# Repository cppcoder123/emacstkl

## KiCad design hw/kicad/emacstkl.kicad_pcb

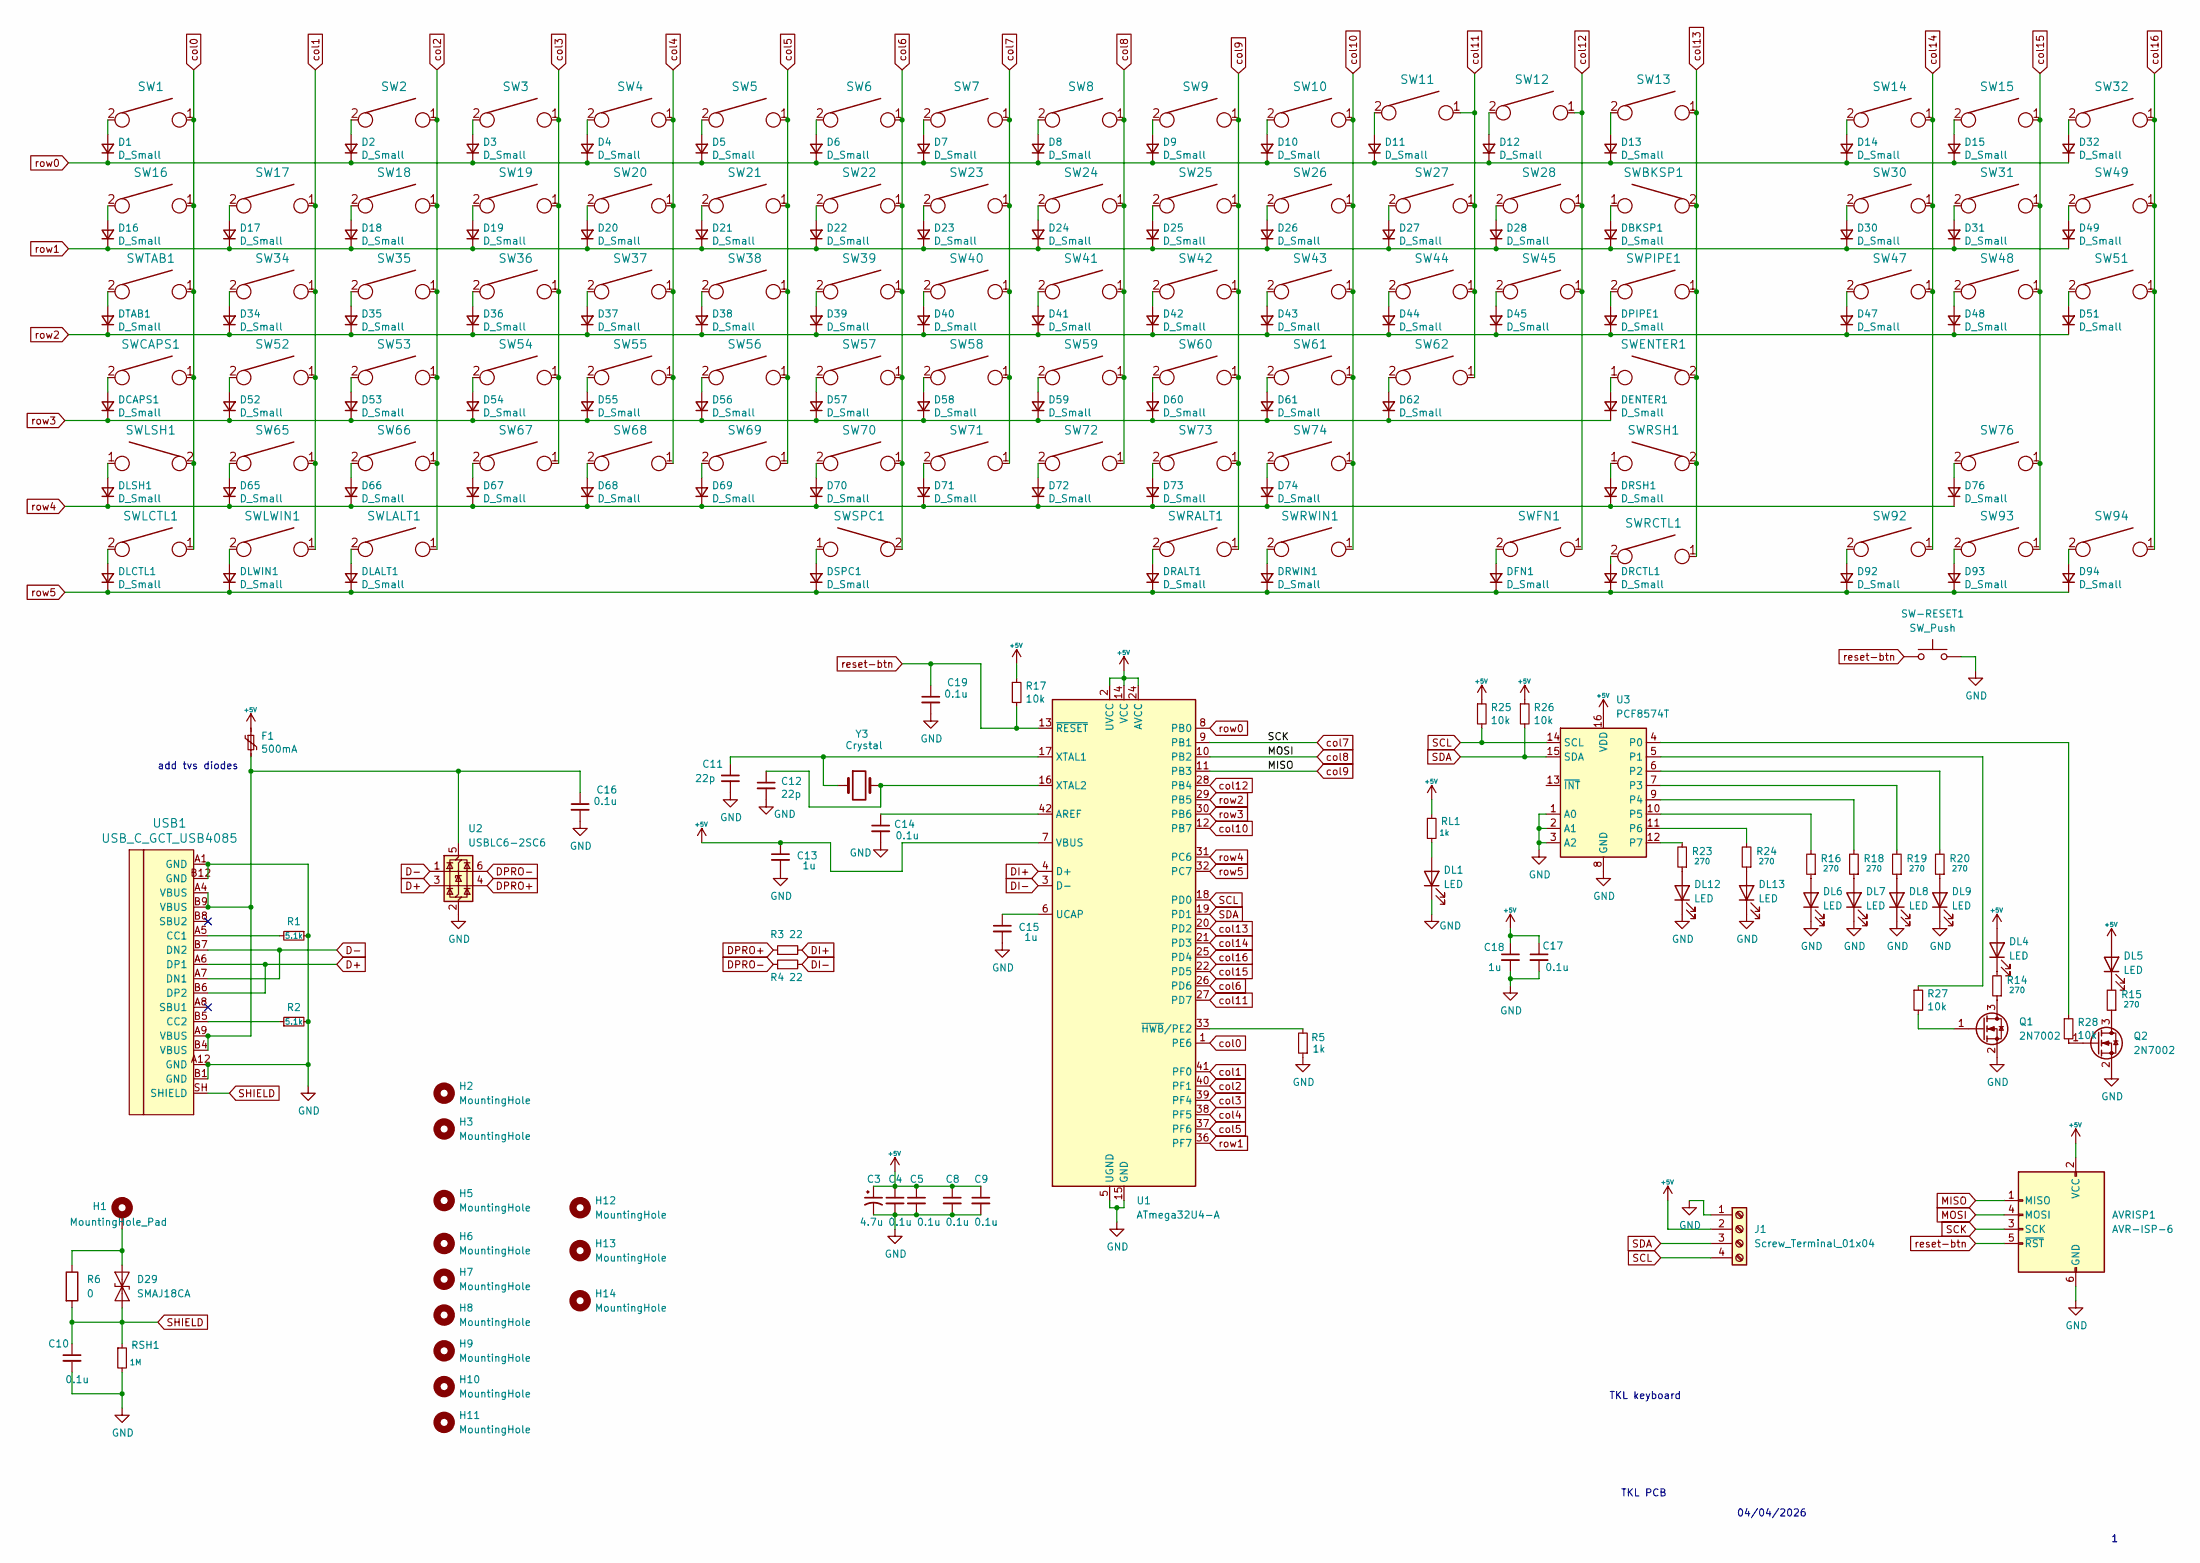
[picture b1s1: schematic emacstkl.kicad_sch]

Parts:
AVRISP1: AVR-ISP-6; PinHeader_2x03_P2.54mm_Vertical
C3: 4.7u; CP_Radial_D4.0mm_P1.50mm_Bend
C4, C5, C8, C9, C10, C14, C16, C17, C19: 0.1u; CP_EIA-3216-18_Kemet-A_HandSolder
C11, C12: 22p; C_1206_3216Metric_Pad1.33x1.80mm_HandSolder
C13, C15, C18: 1u; CP_EIA-3216-18_Kemet-A_HandSolder
D1, D2, D3, D4, D5, D6, D7, D8, D9, D10, D11, D12, D13, D14, D15, D16, D17, D18, D19, D20, D21, D22, D23, D24, D25, D26, D27, D28, D30, D31, D32, D34, D35, D36, D37, D38, D39, D40, D41, D42, D43, D44, D45, D47, D48, D49, D51, D52, D53, D54, D55, D56, D57, D58, D59, D60, D61, D62, D65, D66, D67, D68, D69, D70, D71, D72, D73, D74, D76, D92, D93, D94: D_Small; D_SOD-123
D29: SMAJ18CA; D_SOD-123
DBKSP1: D_Small; D_SOD-123
DCAPS1: D_Small; D_SOD-123
DENTER1: D_Small; D_SOD-123
DFN1: D_Small; D_SOD-123
DL1, DL4, DL5, DL6, DL7, DL8, DL9, DL12, DL13: LED; LED_Kingbright_KPA-3010_3x2x1mm
DLALT1: D_Small; D_SOD-123
DLCTL1: D_Small; D_SOD-123
DLSH1: D_Small; D_SOD-123
DLWIN1: D_Small; D_SOD-123
DPIPE1: D_Small; D_SOD-123
DRALT1: D_Small; D_SOD-123
DRCTL1: D_Small; D_SOD-123
DRSH1: D_Small; D_SOD-123
DRWIN1: D_Small; D_SOD-123
DSPC1: D_Small; D_SOD-123
DTAB1: D_Small; D_SOD-123
F1: 500mA; R_1206_3216Metric_Pad1.30x1.75mm_HandSolder
H1: MountingHole_Pad; MountingHole_4mm_Pad
H2: MountingHole; MountingHole_5mm
H3, H5, H7, H11: MountingHole; MountingHole_6mm
H6: MountingHole; MountingHole_4.5mm
H8, H9, H10: MountingHole; MountingHole_4mm
H12, H13, H14: MountingHole; MountingHole_4.3mm_M4
J1: Screw_Terminal_01x04; JST_EH_B4B-EH-A_1x04_P2.50mm_Vertical
Q1, Q2: 2N7002; SOT-23
R1, R2: 5.1k; R_1206_3216Metric_Pad1.30x1.75mm_HandSolder
R3, R4: 22; R_1206_3216Metric_Pad1.30x1.75mm_HandSolder
R5: 1k; R_1206_3216Metric_Pad1.30x1.75mm_HandSolder
R6: 0; R_1206_3216Metric_Pad1.30x1.75mm_HandSolder
R14, R15, R16, R18, R19, R20, R23, R24: 270; R_1206_3216Metric_Pad1.30x1.75mm_HandSolder
R17, R25, R26, R27, R28: 10k; R_1206_3216Metric_Pad1.30x1.75mm_HandSolder
RL1: 1k; R_1206_3216Metric_Pad1.30x1.75mm_HandSolder
RSH1: 1M; R_1206_3216Metric_Pad1.30x1.75mm_HandSolder
SW1, SW2, SW3, SW4, SW5, SW6, SW7, SW8, SW9, SW10, SW11, SW12, SW13, SW14, SW15, SW16, SW17, SW18, SW19, SW20, SW21, SW22, SW23, SW24, SW25, SW26, SW27, SW28, SW30, SW31, SW32, SW34, SW35, SW36, SW37, SW38, SW39, SW40, SW41, SW42, SW43, SW44, SW45, SW47, SW48, SW49, SW51, SW52, SW53, SW54, SW55, SW56, SW57, SW58, SW59, SW60, SW61, SW62, SW65, SW66, SW67, SW68, SW69, SW70, SW71, SW72, SW73, SW74, SW76, SW92, SW93, SW94: KEYSW; SW_CN_Cherry_MX_PCB_1.00u
SW-RESET1: SW_Push; SW_PUSH_6mm_H4.3mm
SWBKSP1: KEYSW; SW_CN_S_Cherry_MX_2.00u_PCB
SWCAPS1: KEYSW; SW_CN_Cherry_MX_PCB_1.75u
SWENTER1: KEYSW; SW_CN_S_Cherry_MX_2.25u_PCB
SWFN1: KEYSW; SW_CN_Cherry_MX_PCB_1.25u
SWLALT1: KEYSW; SW_CN_Cherry_MX_PCB_1.25u
SWLCTL1: KEYSW; SW_CN_Cherry_MX_PCB_1.25u
SWLSH1: KEYSW; SW_CN_S_Cherry_MX_2.25u_PCB
SWLWIN1: KEYSW; SW_CN_Cherry_MX_PCB_1.25u
SWPIPE1: KEYSW; SW_CN_Cherry_MX_PCB_1.50u
SWRALT1: KEYSW; SW_CN_Cherry_MX_PCB_1.25u
SWRCTL1: KEYSW; SW_CN_Cherry_MX_PCB_1.25u
SWRSH1: KEYSW; SW_CN_S_Cherry_MX_2.75u_PCB
SWRWIN1: KEYSW; SW_CN_Cherry_MX_PCB_1.25u
SWSPC1: KEYSW; SW_CN_S_Cherry_MX_6.25u_PCB
SWTAB1: KEYSW; SW_CN_Cherry_MX_PCB_1.50u
U1: ATmega32U4-A; TQFP-44_10x10mm_P0.8mm
U2: USBLC6-2SC6; SOT-23-6
U3: PCF8574T; SOIC-16W_7.5x10.3mm_P1.27mm
USB1: USB_C_GCT_USB4085; USB_C_Receptacle_GCT_USB4085
Y3: Crystal; Crystal_HC49-4H_Vertical

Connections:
+5V: AVRISP1.2 (VCC), C3.1, C4.1, C5.1, C8.1, C9.1, C13.1, C17.1, C18.1, DL4.2 (A), DL5.2 (A), F1.1, J1.2, R17.1, R25.1, R26.1, RL1.1, U1.2 (UVCC), U1.7 (VBUS), U1.14 (VCC), U1.24 (AVCC), U1.34 (VCC), U1.44 (AVCC), U3.16 (VDD)
D+: U2.3 (I/O2), USB1.A6 (DP1), USB1.B6 (DP2)
D-: U2.1 (I/O1), USB1.A7 (DN1), USB1.B7 (DN2)
DI+: R3.2, U1.4 (D+)
DI-: R4.2, U1.3 (D-)
DPRO+: R3.1, U2.4 (I/O2)
DPRO-: R4.1, U2.6 (I/O1)
GND: AVRISP1.6 (GND), C3.2, C4.2, C5.2, C8.2, C9.2, C10.2, C11.2, C12.2, C13.2, C14.2, C15.2, C16.2, C17.2, C18.2, C19.2, DL1.1 (K), DL6.1 (K), DL7.1 (K), DL8.1 (K), DL9.1 (K), DL12.1 (K), DL13.1 (K), J1.1, Q1.2 (S), Q2.2 (S), R1.1, R2.2, R5.1, RSH1.2, SW-RESET1.2, U1.5 (UGND), U1.15 (GND), U1.23 (GND), U1.35 (GND), U1.43 (GND), U2.2 (GND), U3.1 (A0), U3.2 (A1), U3.3 (A2), U3.8 (GND), USB1.A1 (GND), USB1.A12 (GND), USB1.B1 (GND), USB1.B12 (GND)
MISO: AVRISP1.1 (MISO), SW9.1, SW25.1, SW42.1, SW60.1, SW73.1, SWRALT1.1, U1.11 (PB3)
MOSI: AVRISP1.4 (MOSI), SW8.1, SW24.1, SW41.1, SW59.1, SW72.1, U1.10 (PB2)
unnamed: D1.2 (A), SW1.2
unnamed: D2.2 (A), SW2.2
unnamed: D3.2 (A), SW3.2
unnamed: D4.2 (A), SW4.2
unnamed: D5.2 (A), SW5.2
unnamed: D6.2 (A), SW6.2
unnamed: D7.2 (A), SW7.2
unnamed: D8.2 (A), SW8.2
unnamed: D9.2 (A), SW9.2
unnamed: D10.2 (A), SW10.2
unnamed: D11.2 (A), SW11.2
unnamed: D12.2 (A), SW12.2
unnamed: D13.2 (A), SW13.2
unnamed: D14.2 (A), SW14.2
unnamed: D15.2 (A), SW15.2
unnamed: D16.2 (A), SW16.2
unnamed: D17.2 (A), SW17.2
unnamed: D18.2 (A), SW18.2
unnamed: D19.2 (A), SW19.2
unnamed: D20.2 (A), SW20.2
unnamed: D21.2 (A), SW21.2
unnamed: D22.2 (A), SW22.2
unnamed: D23.2 (A), SW23.2
unnamed: D24.2 (A), SW24.2
unnamed: D25.2 (A), SW25.2
unnamed: D26.2 (A), SW26.2
unnamed: D27.2 (A), SW27.2
unnamed: D28.2 (A), SW28.2
unnamed: D29.2 (A2), H1.1 (1_1), R6.1
unnamed: D30.2 (A), SW30.2
unnamed: D31.2 (A), SW31.2
unnamed: D32.2 (A), SW32.2
unnamed: D34.2 (A), SW34.2
unnamed: D35.2 (A), SW35.2
unnamed: D36.2 (A), SW36.2
unnamed: D37.2 (A), SW37.2
unnamed: D38.2 (A), SW38.2
unnamed: D39.2 (A), SW39.2
unnamed: D40.2 (A), SW40.2
unnamed: D41.2 (A), SW41.2
unnamed: D42.2 (A), SW42.2
unnamed: D43.2 (A), SW43.2
unnamed: D44.2 (A), SW44.2
unnamed: D45.2 (A), SW45.2
unnamed: D47.2 (A), SW47.2
unnamed: D48.2 (A), SW48.2
unnamed: D49.2 (A), SW49.2
unnamed: D51.2 (A), SW51.2
unnamed: D52.2 (A), SW52.2
unnamed: D53.2 (A), SW53.2
unnamed: D54.2 (A), SW54.2
unnamed: D55.2 (A), SW55.2
unnamed: D56.2 (A), SW56.2
unnamed: D57.2 (A), SW57.2
unnamed: D58.2 (A), SW58.2
unnamed: D59.2 (A), SW59.2
unnamed: D60.2 (A), SW60.2
unnamed: D61.2 (A), SW61.2
unnamed: D62.2 (A), SW62.2
unnamed: D65.2 (A), SW65.2
unnamed: D66.2 (A), SW66.2
unnamed: D67.2 (A), SW67.2
unnamed: D68.2 (A), SW68.2
unnamed: D69.2 (A), SW69.2
unnamed: D70.2 (A), SW70.2
unnamed: D71.2 (A), SW71.2
unnamed: D72.2 (A), SW72.2
unnamed: D73.2 (A), SW73.2
unnamed: D74.2 (A), SW74.2
unnamed: D76.2 (A), SW76.2
unnamed: D92.2 (A), SW92.2
unnamed: D93.2 (A), SW93.2
unnamed: D94.2 (A), SW94.2
unnamed: DBKSP1.2 (A), SWBKSP1.1
unnamed: DCAPS1.2 (A), SWCAPS1.2
unnamed: DENTER1.2 (A), SWENTER1.1
unnamed: DFN1.2 (A), SWFN1.2
unnamed: DL1.2 (A), RL1.2
unnamed: DL4.1 (K), R14.2
unnamed: DL5.1 (K), R15.2
unnamed: DL6.2 (A), R16.1
unnamed: DL7.2 (A), R18.1
unnamed: DL8.2 (A), R19.1
unnamed: DL9.2 (A), R20.1
unnamed: DL12.2 (A), R23.1
unnamed: DL13.2 (A), R24.1
unnamed: DLALT1.2 (A), SWLALT1.2
unnamed: DLCTL1.2 (A), SWLCTL1.2
unnamed: DLSH1.2 (A), SWLSH1.1
unnamed: DLWIN1.2 (A), SWLWIN1.2
unnamed: DPIPE1.2 (A), SWPIPE1.2
unnamed: DRALT1.2 (A), SWRALT1.2
unnamed: DRCTL1.2 (A), SWRCTL1.2
unnamed: DRSH1.2 (A), SWRSH1.1
unnamed: DRWIN1.2 (A), SWRWIN1.2
unnamed: DSPC1.2 (A), SWSPC1.1
unnamed: DTAB1.2 (A), SWTAB1.2
unnamed: Q1.3 (D), R14.1
unnamed: Q1.1 (G), R27.2
unnamed: Q2.3 (D), R15.1
unnamed: Q2.1 (G), R28.2
unnamed: C14.1, U1.42 (AREF)
unnamed: C15.1, U1.6 (UCAP)
unnamed: C11.1, U1.17 (XTAL1), Y3.1
unnamed: C12.1, U1.16 (XTAL2), Y3.2
unnamed: R5.2, U1.33 (~HWB/PE2)
unnamed: C16.1, F1.2, U2.5 (VBUS), USB1.A4 (VBUS), USB1.A9 (VBUS), USB1.B4 (VBUS), USB1.B9 (VBUS)
unnamed: R28.1, U3.4 (P0)
unnamed: R27.1, U3.5 (P1)
unnamed: R20.2, U3.6 (P2)
unnamed: R19.2, U3.7 (P3)
unnamed: R18.2, U3.9 (P4)
unnamed: R16.2, U3.10 (P5)
unnamed: R24.2, U3.11 (P6)
unnamed: R23.2, U3.12 (P7)
unnamed: R1.2, USB1.A5 (CC1)
unnamed: R2.1, USB1.B5 (CC2)
SCK: AVRISP1.3 (SCK), SW7.1, SW23.1, SW40.1, SW58.1, SW71.1, U1.9 (PB1)
SCL: J1.4, R25.2, U1.18 (PD0), U3.14 (SCL)
SDA: J1.3, R26.2, U1.19 (PD1), U3.15 (SDA)
SHIELD: C10.1, D29.1 (A1), R6.2, RSH1.1, USB1.SH (SHIELD)
col0: SW1.1, SW16.1, SWCAPS1.1, SWLCTL1.1, SWLSH1.2, SWTAB1.1, U1.1 (PE6)
col1: SW17.1, SW34.1, SW52.1, SW65.1, SWLWIN1.1, U1.41 (PF0)
col2: SW2.1, SW18.1, SW35.1, SW53.1, SW66.1, SWLALT1.1, U1.40 (PF1)
col3: SW3.1, SW19.1, SW36.1, SW54.1, SW67.1, U1.39 (PF4)
col4: SW4.1, SW20.1, SW37.1, SW55.1, SW68.1, U1.38 (PF5)
col5: SW5.1, SW21.1, SW38.1, SW56.1, SW69.1, U1.37 (PF6)
col6: SW6.1, SW22.1, SW39.1, SW57.1, SW70.1, SWSPC1.2, U1.26 (PD6)
col10: SW10.1, SW26.1, SW43.1, SW61.1, SW74.1, SWRWIN1.1, U1.12 (PB7)
col11: SW11.1, SW27.1, SW44.1, SW62.1, U1.27 (PD7)
col12: SW12.1, SW28.1, SW45.1, SWFN1.1, U1.28 (PB4)
col13: SW13.1, SWBKSP1.2, SWENTER1.2, SWPIPE1.1, SWRCTL1.1, SWRSH1.2, U1.20 (PD2)
col14: SW14.1, SW30.1, SW47.1, SW92.1, U1.21 (PD3)
col15: SW15.1, SW31.1, SW48.1, SW76.1, SW93.1, U1.22 (PD5)
col16: SW32.1, SW49.1, SW51.1, SW94.1, U1.25 (PD4)
reset-btn: AVRISP1.5 (~RST), C19.1, R17.2, SW-RESET1.1, U1.13 (~RESET)
row0: D1.1 (K), D2.1 (K), D3.1 (K), D4.1 (K), D5.1 (K), D6.1 (K), D7.1 (K), D8.1 (K), D9.1 (K), D10.1 (K), D11.1 (K), D12.1 (K), D13.1 (K), D14.1 (K), D15.1 (K), D32.1 (K), U1.8 (PB0)
row1: D16.1 (K), D17.1 (K), D18.1 (K), D19.1 (K), D20.1 (K), D21.1 (K), D22.1 (K), D23.1 (K), D24.1 (K), D25.1 (K), D26.1 (K), D27.1 (K), D28.1 (K), D30.1 (K), D31.1 (K), D49.1 (K), DBKSP1.1 (K), U1.36 (PF7)
row2: D34.1 (K), D35.1 (K), D36.1 (K), D37.1 (K), D38.1 (K), D39.1 (K), D40.1 (K), D41.1 (K), D42.1 (K), D43.1 (K), D44.1 (K), D45.1 (K), D47.1 (K), D48.1 (K), D51.1 (K), DPIPE1.1 (K), DTAB1.1 (K), U1.29 (PB5)
row3: D52.1 (K), D53.1 (K), D54.1 (K), D55.1 (K), D56.1 (K), D57.1 (K), D58.1 (K), D59.1 (K), D60.1 (K), D61.1 (K), D62.1 (K), DCAPS1.1 (K), DENTER1.1 (K), U1.30 (PB6)
row4: D65.1 (K), D66.1 (K), D67.1 (K), D68.1 (K), D69.1 (K), D70.1 (K), D71.1 (K), D72.1 (K), D73.1 (K), D74.1 (K), D76.1 (K), DLSH1.1 (K), DRSH1.1 (K), U1.31 (PC6)
row5: D92.1 (K), D93.1 (K), D94.1 (K), DFN1.1 (K), DLALT1.1 (K), DLCTL1.1 (K), DLWIN1.1 (K), DRALT1.1 (K), DRCTL1.1 (K), DRWIN1.1 (K), DSPC1.1 (K), U1.32 (PC7)

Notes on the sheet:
TKL keyboard
TKL PCB
add tvs diodes
04/04/2026

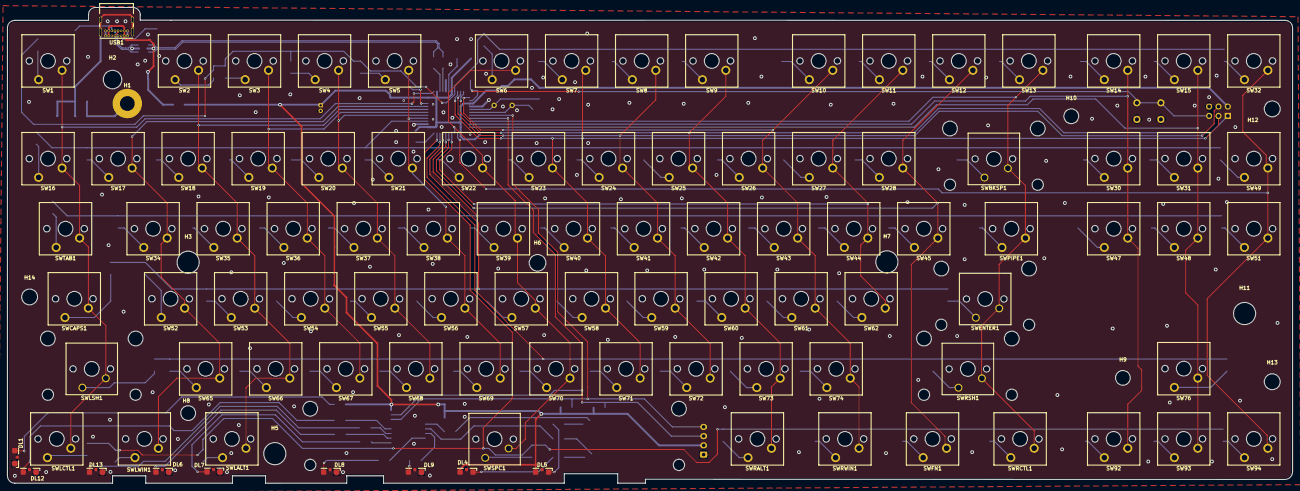
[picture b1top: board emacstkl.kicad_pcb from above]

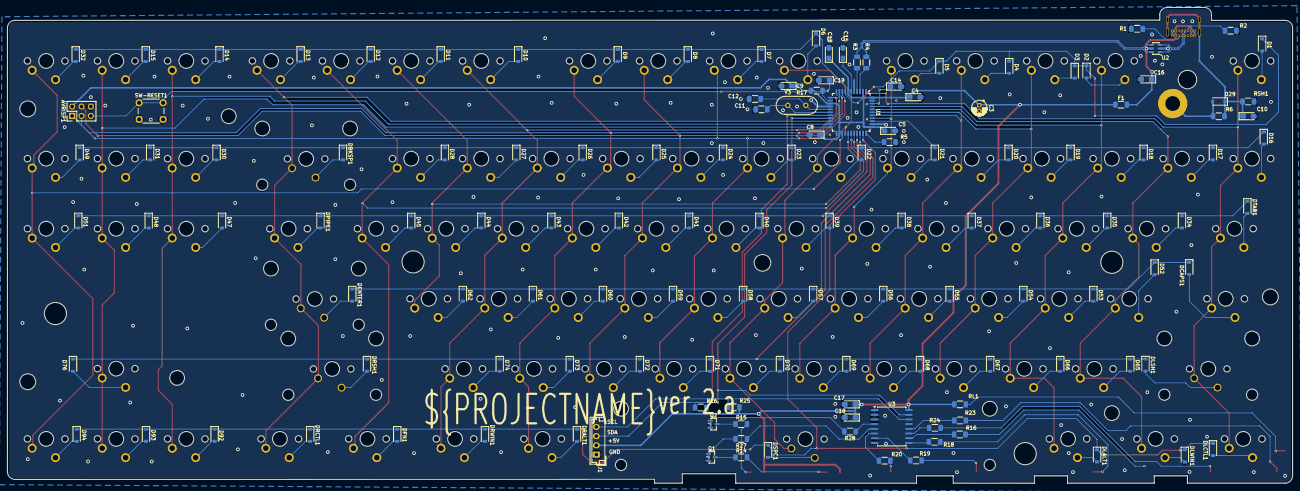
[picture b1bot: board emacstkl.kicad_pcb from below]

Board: 2 copper layers, 348.5 x 129.0 mm, 244 parts (134 on the bottom side), 152 nets.

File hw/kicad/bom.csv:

Designator,Footprint,Quantity,Value,LCSC Part #
AVRISP1,PinHeader_2x03_P2.54mm_Vertical,1,AVR-ISP-6,
"C10, C14, C16, C17, C19, C4, C5, C8, C9",CP_EIA-3216-18_Kemet-A_HandSolder,9,0.1u,
"C11, C12",1206,2,22p,
"C13, C15, C18",CP_EIA-3216-18_Kemet-A_HandSolder,3,1u,
C3,CP_Radial_D4.0mm_P1.50mm_Bend,1,4.7u,
"D1, D10, D11, D12, D13, D14, D15, D16, D17, D18, D19, D2, D20, D21, D22, D23, D24, D25, D26, D27, D28, D3, D30, D31, D32, D34, D35, D36, D37, D38, D39, D4, D40, D41, D42, D43, D44, D45, D47, D48, D49, D5, D51, D52, D53, D54, D55, D56, D57, D58, D59, D6, D60, D61, D62, D65, D66, D67, D68, D69, D7, D70, D71, D72, D73, D74, D76, D8, D9, D92, D93, D94, DBKSP1, DCAPS1, DENTER1, DFN1, DLALT1, DLCTL1, DLSH1, DLWIN1, DPIPE1, DRALT1, DRCTL1, DRSH1, DRWIN1, DSPC1, DTAB1",D_SOD-123,87,D_Small,
D29,D_SOD-123,1,SMAJ18CA,
"DL1, DL12, DL13, DL4, DL5, DL6, DL7, DL8, DL9",LED_Kingbright_KPA-3010_3x2x1mm,9,LED,
F1,1206,1,500mA,
J1,JST_EH_B4B-EH-A_1x04_P2.50mm_Vertical,1,Screw_Terminal_01x04,
"Q1, Q2",SOT-23,2,2N7002,
"R1, R2",1206,2,5.1k,
"R14, R15, R16, R18, R19, R20, R23, R24",1206,8,270,
"R17, R25, R26, R27, R28",1206,5,10k,
"R3, R4",1206,2,22,
"R5, RL1",1206,2,1k,
R6,1206,1,0,
RSH1,1206,1,1M,
SW-RESET1,SW_PUSH_6mm_H4.3mm,1,SW_Push,
"SW1, SW10, SW11, SW12, SW13, SW14, SW15, SW16, SW17, SW18, SW19, SW2, SW20, SW21, SW22, SW23, SW24, SW25, SW26, SW27, SW28, SW3, SW30, SW31, SW32, SW34, SW35, SW36, SW37, SW38, SW39, SW4, SW40, SW41, SW42, SW43, SW44, SW45, SW47, SW48, SW49, SW5, SW51, SW52, SW53, SW54, SW55, SW56, SW57, SW58, SW59, SW6, SW60, SW61, SW62, SW65, SW66, SW67, SW68, SW69, SW7, SW70, SW71, SW72, SW73, SW74, SW76, SW8, SW9, SW92, SW93, SW94",SW_CN_Cherry_MX_PCB_1.00u,72,KEYSW,
SWBKSP1,SW_CN_S_Cherry_MX_2.00u_PCB,1,KEYSW,
SWCAPS1,SW_CN_Cherry_MX_PCB_1.75u,1,KEYSW,
"SWENTER1, SWLSH1",SW_CN_S_Cherry_MX_2.25u_PCB,2,KEYSW,
"SWFN1, SWLALT1, SWLCTL1, SWLWIN1, SWRALT1, SWRCTL1, SWRWIN1",SW_CN_Cherry_MX_PCB_1.25u,7,KEYSW,
"SWPIPE1, SWTAB1",SW_CN_Cherry_MX_PCB_1.50u,2,KEYSW,
SWRSH1,SW_CN_S_Cherry_MX_2.75u_PCB,1,KEYSW,
SWSPC1,SW_CN_S_Cherry_MX_6.25u_PCB,1,KEYSW,
U1,TQFP-44_10x10mm_P0.8mm,1,ATmega32U4-A,
U2,SOT-23-6,1,USBLC6-2SC6,
U3,SOIC-16W_7.5x10.3mm_P1.27mm,1,PCF8574T,
USB1,USB_C_Receptacle_GCT_USB4085,1,USB_C_GCT_USB4085,
Y3,Crystal_HC49-4H_Vertical,1,Crystal,

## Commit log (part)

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2026-04-29 hw: Add 1.a files
2026-05-02 change license
2026-05-02 Create LICENSE
2026-05-02 src: Add fw files
2026-05-02 keymap: Start adding macros
2026-05-02 keymap: Fix and add comments
2026-05-02 keymap: Add one led handling
2026-05-02 keymap: Name layers
2026-05-02 keymap: Add spaces
2026-05-02 keymap: Use LT to switch to layer-1
2026-05-03 keymap: Add comments
2026-05-04 keymap: Generate keymaps using awk
2026-05-04 keymap-awk: Polish the name
2026-05-04 keymap-awk: Rename 'add' -> 'map'
2026-05-05 keymap: Use KC_TRNS for Caps-lock at layer 1
2026-05-05 keymap: Port to new version, add keys - not implemented
2026-05-05 keymap: Add ctl-alt-del
2026-05-06 keymap: Implement more keys
2026-05-07 keymap-awk: Remove commented code
2026-05-07 hw: Add kicad files
2026-05-11 keymap: Add layers 2 & 3 to test leds
2026-05-11 keymap: Save leds debug session
2026-05-14 config: Disable extra-keys
2026-05-14 keymap: Fix macros
2026-05-15 keymap: Add avy macro
2026-05-25 keyboard-json: Update for hw-2a
2026-06-01 fw: Add home-row mods
2026-06-04 keymap: Define 3 layers home-row, emacs, tmux
2026-06-08 rules-mk: Enable i2c, disable mouse-keys
